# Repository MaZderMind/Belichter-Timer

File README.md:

= Belichter-Timer =
Meine Version eines ATTiny gesteuerten Belichterkasten-Timers. Der Belichterkasten wird von UV-LEDs betrieben und hier beschrieben:
http://microdrum.wordpress.com/2012/03/11/platinen-herstellen-fortsetzung/

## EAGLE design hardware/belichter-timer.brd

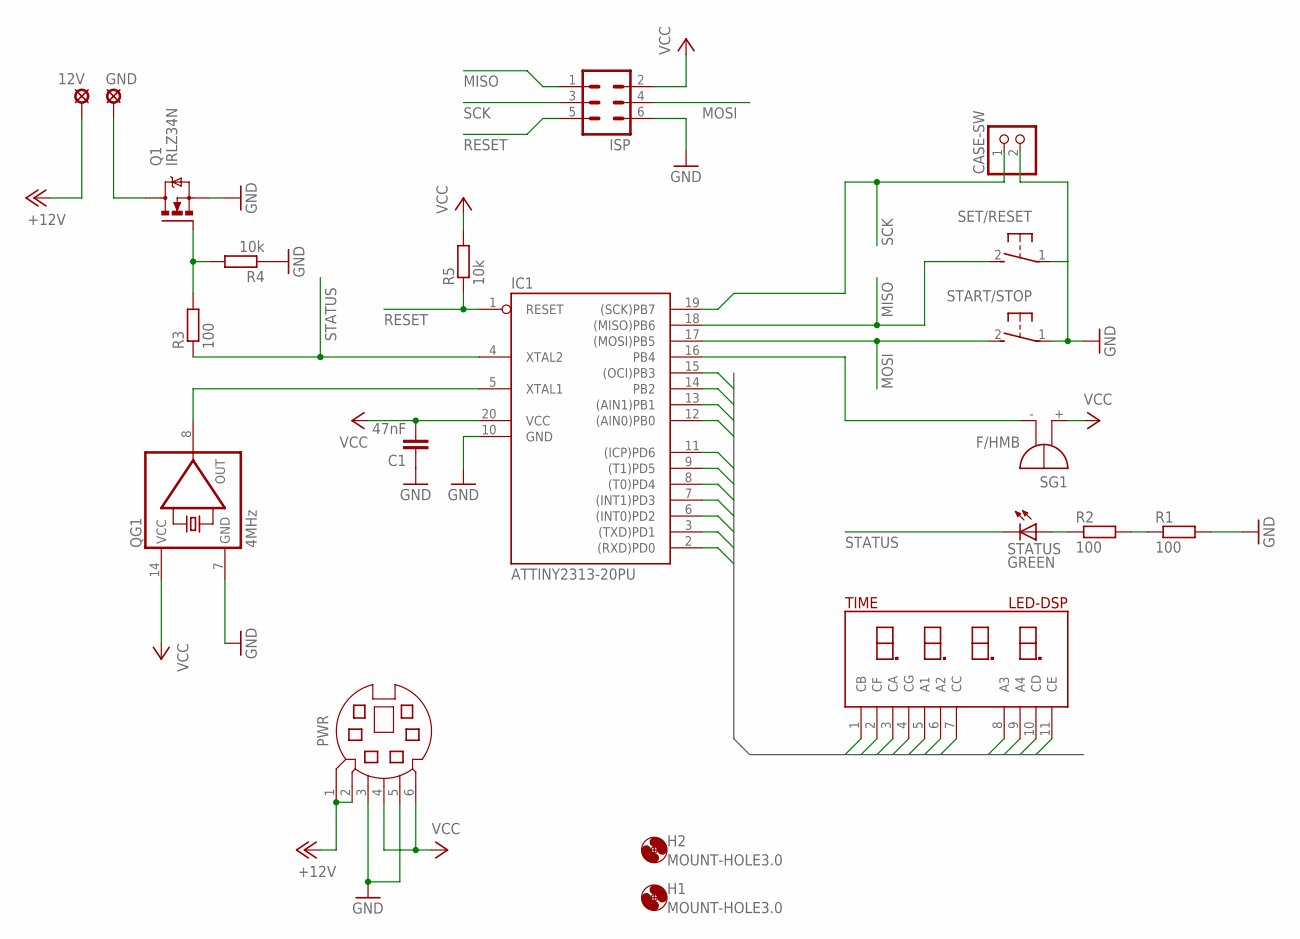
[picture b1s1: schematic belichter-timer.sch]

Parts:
12V: SE14
C1: 47nF; C075-032X103
CASE-SW: PINHD-1X2; 1X02
GND: SE14
H1, H2: MOUNT-HOLE3.0; 3,0
IC1: ATTINY2313-20PU; DIL20
ISP: ML6
PWR: MD06SS; MDIN06SS
Q1: IRLZ34N; TO220BH
QG1: 4MHz; DIL14S
R1, R2, R3: 100; 0204/7
R4, R5: 10k; 0204/7
SET/RESET: 31-XX; B3F-31XX
SG1: F/HMB
START/STOP: 31-XX; B3F-31XX
STATUS: GREEN; LED5MM
TIME: LED-DSP

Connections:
+12V: 12V.MP, PWR.1, PWR.2
CLK: IC1.5 (XTAL1), QG1.8 (OUT)
DP0: IC1.11 ((ICP)PD6), TIME.7 (CC)
DP1: IC1.9 ((T1)PD5), TIME.6 (A2)
DP2: IC1.8 ((T0)PD4), TIME.5 (A1)
DP3: IC1.7 ((INT1)PD3), TIME.4 (CG)
DP4: IC1.6 ((INT0)PD2), TIME.3 (CA)
DP5: IC1.3 ((TXD)PD1), TIME.2 (CF)
DP6: IC1.2 ((RXD)PD0), TIME.1 (CB)
DPA: IC1.15 ((OCI)PB3), TIME.11 (CE)
DPB: IC1.14 (PB2), TIME.10 (CD)
DPC: IC1.13 ((AIN1)PB1), TIME.9 (A4)
DPD: IC1.12 ((AIN0)PB0), TIME.8 (A3)
GND: C1.1, CASE-SW.2, IC1.10 (GND), ISP.6, PWR.3, PWR.5, Q1.S, QG1.7 (GND), R1.2, R4.1, SET/RESET.1, START/STOP.1
LOAD_GND: GND.MP, Q1.D
MISO: IC1.18 ((MISO)PB6), ISP.1, SET/RESET.2 (S)
MOSI: IC1.17 ((MOSI)PB5), ISP.4, START/STOP.2 (S)
unnamed: R2.1, STATUS.A
unnamed: R1.1, R2.2
unnamed: Q1.G, R3.2, R4.2
RESET: IC1.1 (RESET), ISP.5, R5.1
SCK: CASE-SW.1, IC1.19 ((SCK)PB7), ISP.3
SND: IC1.16 (PB4), SG1.-
STATUS: IC1.4 (XTAL2), R3.1, STATUS.K (C)
VCC: C1.2, IC1.20 (VCC), ISP.2, PWR.4, PWR.6, QG1.14 (VCC), R5.2, SG1.+

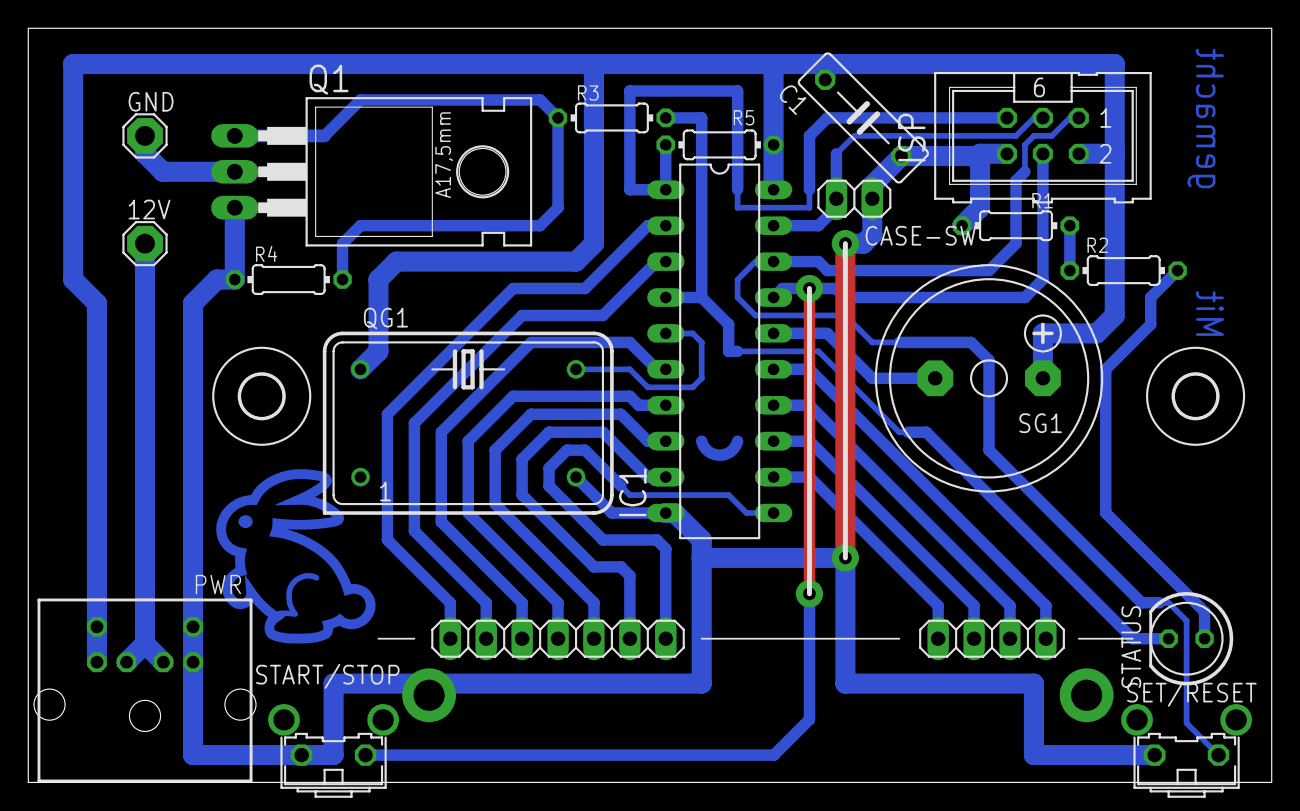
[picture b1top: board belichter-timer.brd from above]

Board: 2 copper layers, 87.9 x 53.3 mm, 21 parts (0 on the bottom side), 25 nets.

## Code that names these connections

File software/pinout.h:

#define DDR_A1 DDRD
#define PORT_A1 PORTD
#define P_A1 PD4

#define DDR_A2 DDRD
#define PORT_A2 PORTD
#define P_A2 PD5

#define DDR_A3 DDRB
#define PORT_A3 PORTB
#define P_A3 PB0

#define DDR_A4 DDRB
#define PORT_A4 PORTB
#define P_A4 PB1



#define DDR_CA DDRD
#define PORT_CA PORTD
#define P_CA PD2

#define DDR_CB DDRD
#define PORT_CB PORTD
#define P_CB PD0

#define DDR_CC DDRD
#define PORT_CC PORTD
#define P_CC PD6

#define DDR_CD DDRB
#define PORT_CD PORTB
#define P_CD PB2

#define DDR_CE DDRB
#define PORT_CE PORTB
#define P_CE PB3

#define DDR_CF DDRD
#define PORT_CF PORTD
#define P_CF PD1

#define DDR_CG DDRD
#define PORT_CG PORTD
#define P_CG PD3



#define DDR_RESET DDRB
#define PORT_RESET PORTB
#define PIN_RESET PINB
#define P_RESET PB5
#define PCINT_RESET PCINT5

#define DDR_START DDRB
#define PORT_START PORTB
#define PIN_START PINB
#define P_START PB6
#define PCINT_START PCINT6

#define DDR_CASE DDRB
#define PORT_CASE PORTB
#define PIN_CASE PINB
#define P_CASE PB7
#define PCINT_CASE PCINT7


#define DDR_MOSFET DDRA
#define PORT_MOSFET PORTA
#define P_MOSFET PA1

#define DDR_SND DDRB
#define PORT_SND PORTB
#define P_SND PB4

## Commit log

2013-10-03 need a repo by now
2013-10-08 display subsystem w/ demo
2013-10-08 test display functions
2013-10-08 for the records
2013-10-08 real time clock & button interface
2013-10-08 reset counter to 0 on value set
2013-10-08 switch load with timer
2013-10-08 switch load of when the timer reaches 0, not 1 second later
2013-10-08 write sth. more about the led-display
2013-10-08 forgot to add the (very simple, indeed) mosfet driving code
2013-10-08 start/stop logic, wait for user input
2013-10-08 subfolders
2013-10-08 documentation pdfs
2013-10-08 a little readme
2013-10-08 add BSD License
2013-10-20 remove whitespace
2013-10-20 fix function header
2013-10-20 fix description, use real measured values
2013-10-20 fix comment, whitespace and function header
2013-10-20 add segment description
2013-10-22 snd output
2013-10-22 implement debouncing and a general available RUNTIME const.
2013-10-22 measures and explanations around the display driving and the button debouncing
2013-10-23 typo
2013-10-23 setmode enter & leave
2013-10-26 change counter setup to avoid 1Hz error
2013-10-27 use double-press as setmode indicator
2013-10-27 store runtime in eeprom and make it truely settable
2013-10-27 use a higher value for the debounce value to help pressing both buttons in the set mode more easy without changing the value
2013-10-29 fuse codes
2014-01-01 case open detection
2014-01-01 force some functions to be inline, reduces required space
2014-01-01 fit a beep routine into the device
2014-01-02 reorder includes
2014-01-02 fix display rotation to match mounting position
